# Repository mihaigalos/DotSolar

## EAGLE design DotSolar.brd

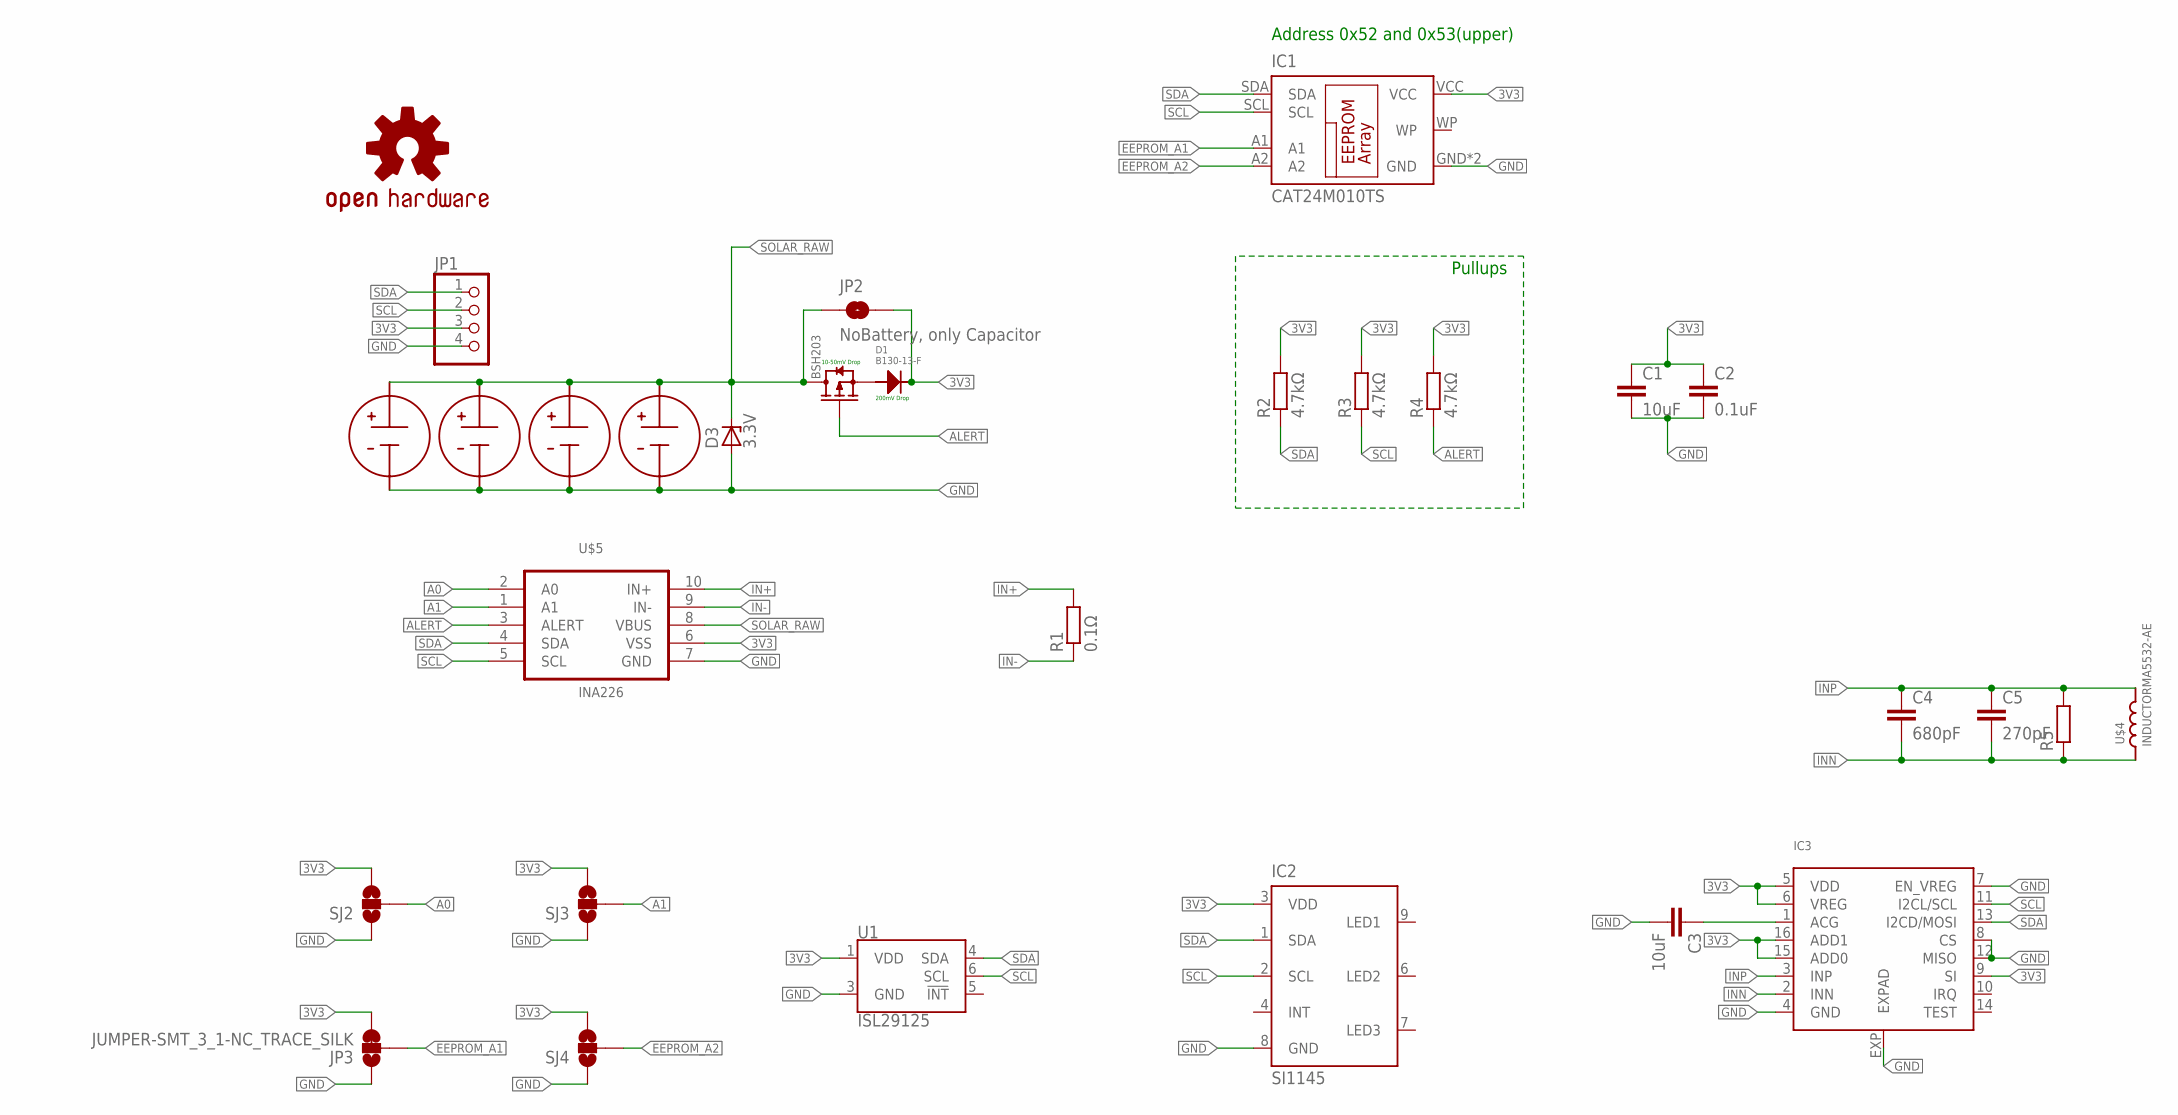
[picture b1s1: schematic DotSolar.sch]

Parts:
C1, C3: 10uF; C0603
C2: 0.1uF; C0603
C4: 680pF; C0603
C5: 270pF; C0603
D1: B130-13-F
D3: 3.3V; SMB
IC1: CAT24M010TS; TSSOP8
IC2: SI1145; QFN-10
IC3: AS3935; 16LDMLPQ
JP1: PINHD-1X4; 1X04
JP2: NoBattery, only Capacitor; SMT-JUMPER_2_NO_SILK
JP3: JUMPER-SMT_3_1-NC_TRACE_SILK; SMT-JUMPER_3_1-NC_TRACE_SILK
LOGO1: OSHW-LOGOS; OSHW-LOGO-S
Q1: BSH203; SOT-23
R1: 0.1Ω; R0603
R2, R3, R4: 4.7kΩ; R0603
R5: R-EU_R0603; R0603
SJ2, SJ3, SJ4: SOLDERJUMPER_2WAYPASTE2&3; SJ_3_PASTE2&3
U1: ISL29125; ODFN-6
U$1, U$2, U$3, U$6: KXOB22-01X8F_EXTENDED_PADS
U$4: INDUCTORMA5532-AE; MA5532-AE
U$5: INA226; VSSOP-10

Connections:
3V3: C1.1, C2.1, D1.CATHODE, IC1.VCC, IC2.3 (VDD), IC3.5 (VDD), IC3.6 (VREG), IC3.9 (SI), IC3.15 (ADD0), IC3.16 (ADD1), JP1.3, JP2.2, JP3.3, R2.2, R3.2, R4.2, SJ2.3, SJ3.3, SJ4.3, U1.1 (VDD), U$5.6 (VSS)
A0: SJ2.2, U$5.2 (A0)
A1: SJ3.2, U$5.1 (A1)
ALERT: Q1.1 (G), R4.1, U$5.3 (ALERT)
EEPROM_A1: IC1.A1, JP3.2
EEPROM_A2: IC1.A2, SJ4.2
GND: C1.2, C2.2, C3.2, D3.A, IC1.GND, IC1.NC (GND), IC2.8 (GND), IC3.4 (GND), IC3.7 (EN_VREG), IC3.8 (CS), IC3.12 (MISO), IC3.EXP (EXPAD), JP1.4, JP3.1, SJ2.1, SJ3.1, SJ4.1, U1.3 (GND), U$1.P$1, U$2.P$1, U$3.P$1, U$5.7 (GND), U$6.P$1
IN+: R1.2, U$5.10 (IN+)
IN-: R1.1, U$5.9 (IN-)
INN: C4.2, C5.2, IC3.2 (INN), R5.1, U$4.2
INP: C4.1, C5.1, IC3.3 (INP), R5.2, U$4.1
unnamed: D1.ANODE, Q1.2 (S)
unnamed: C3.1, IC3.1 (ACG)
SCL: IC1.SCL, IC2.2 (SCL), IC3.11 (I2CL/SCL), JP1.2, R3.1, U1.6 (SCL), U$5.5 (SCL)
SDA: IC1.SDA, IC2.1 (SDA), IC3.13 (I2CD/MOSI), JP1.1, R2.1, U1.4 (SDA), U$5.4 (SDA)
SOLAR_RAW: D3.C, JP2.1, Q1.3 (D), U$1.P$2, U$2.P$2, U$3.P$2, U$5.8 (VBUS), U$6.P$2

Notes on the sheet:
10-50mV Drop
200mV Drop
Pullups
Address 0x52 and 0x53(upper)

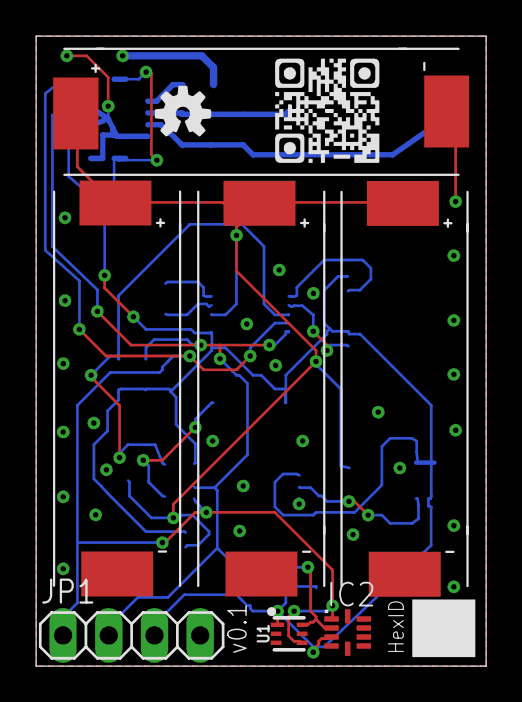
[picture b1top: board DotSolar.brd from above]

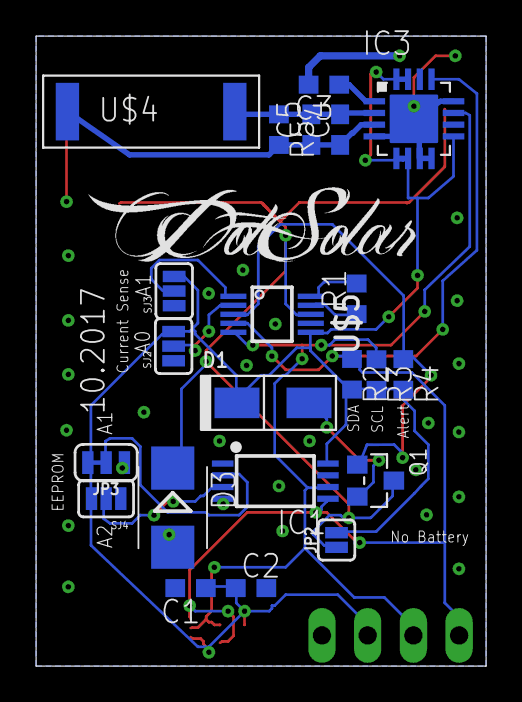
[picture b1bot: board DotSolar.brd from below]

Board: 2 copper layers, 25.0 x 35.0 mm, 30 parts (22 on the bottom side), 16 nets.

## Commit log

2017-07-23 Update with exdended solar pad design
2017-07-23 Spacing cells further apart
2017-07-23 Add C1(10uF) and C2(1uF)
2017-07-23 Add GND planes
2017-07-23 Add CAT24M01 8Mbit EEPROM
2017-07-23 EEPROM default address 0x52 and 0x53
2017-07-23 Move zener
2017-08-01 Update tracks for production at Aisler
2017-08-02 Add AS3935 lightning detector

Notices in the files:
parts and their libraries:
Particle-Devices: Licensing: Designed by Particle.
SparkFun: Licensing: CC v3.0 Share-Alike You are welcome to use this library for commercial purposes.
SparkFun-Sensors: Licensing: Creative Commons ShareAlike 4.0 International - https://creativecommons.org/licenses/by-sa/4.0
